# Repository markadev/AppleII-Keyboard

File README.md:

# Apple II Keyboard Adapter

This is a simple Arduino project to allow connecting a PS/2 keyboard to the
16 pin DIP keyboard connector on an Apple II. I've tested it on a
ReactiveMicro reproduction Apple II+ RFI logic board and it works great.

All keys are mapped to modern keyboard equivalents and the Apple can be
reset with the Ctrl-PrtScrn key combo.

I've built this project two different ways - the original prototype with a cheap Arduino Pro
Micro clone, and a newer version that consolidates all the wiring onto a small PCB with an
ATtiny24a microcontroller. This is very much a DIY project.

## ATtiny24a version

This version of the keyboard adapter is pretty simple and also includes a footprint for optional
ESD protection diodes to protect your Apple II from static discharges through the PS/2 interface.
It will require an ATtiny ISP (In-system Programmer) like the XGecu T48 or similar, or an Arduino
running the ArduinoISP sketch could also work.

It's composed of two parts: an adapter board with a microcontroller for performing the
translation logic and a connector board with the PS/2 keyboard connector that can be mounted
separately. If you want to use a different type of PS/2 connector then you are free to wire
up anything you need to the 8 pin header on the adapter board! For example, I can use an old
PC screw-mounted PS/2 connector.

### Building

This repo contains all the source files for building a Keyboard Adapter:
 * [KiCad project for the adapter board](./AppleII-Keyboard)
 * [KiCad project for a mountable PS/2 connector board](./AppleII-Keyboard-Connector)
 * [Source code for the microcontroller](./src/AppleII_PS2_Keyboard)

All the output files are also included so you don't need to install KiCad or the Arduino IDE if
you don't want to.
 * Schematics for the [adapter board](./AppleII-Keyboard/AppleII-Keyboard.pdf) and [connector board](./AppleII-Keyboard-Connector/AppleII-Keyboard-Connector.pdf)
 * Gerber files for the [adapter board](./AppleII-Keyboard/outputs/) and [connector board](./AppleII-Keyboard-Connector/outputs/)
 * [Pre-compiled ATtiny code](./src/AppleII_PS2_Keyboard/build/diy_attiny.avr.attiny24_diy/AppleII_PS2_Keyboard.ino.hex) to flash into the ATtiny

#### Parts List

Most of the parts are commodity and can be substituted for others, except for the ATtiny and the
ESD protection diodes. The ESD diodes are OPTIONAL so can be omitted if you can't find them or have
difficulty soldering the small surface-mount part.

You'll need one of each PCB; one PCB for the adapter that plugs into the keyboard connector on the
Apple II logic board and one PCB for the PS/2 mini-DIN connector board.

| Qty | Value                     | Mfr                 | MfrPartNo          | MouserPartNo         |
|-----|---------------------------|---------------------|--------------------|----------------------|
|  1  | 1x16 Machine Pin Header   | Samtec              | TS-116-T-A         | 200-TS116TA          |
|  1  | DIP-14 Socket             | TE Connectivity     | 1-2199298-3        | 571-1-2199298-3      |
|  1  | ATtiny24a                 | Microchip           | ATTINY24A-PU       | 556-ATTINY24A-PU     |
|  1  | 0.1uF                     | Vishay              | A104K15X7RF5TAA    | 594-A104K15X7RF5TAA  |
|  1  | Breakaway 2x8 pin headers | Amphenol            | 10129381-916001BLF | 649-1012938191601BLF |
|  1  | ESD Protection Diodes     | Diodes Incorporated | DT2042-04TS-7      | 621-DT2042-04TS-7    |
|  1  | Mini-DIN-6 connector      | Kycon               | KMDGX-6S-BS        | 806-KMDGX-6S-BS      |
|  2  | 2x4P IDC cable housing    | Amphenol            | 71600-008LF        | 649-71600-008LF      |

In addition to these components you will also need some 8 conductor 1.27mm pitch ribbon cable for
the cable between the adapter board and the connector board, as long as you need to reach wherever
you'll be mounting the PS/2 connector. This type of ribbon cable can be scavenged from common internal
cables that were used in old PCs.

#### Assembling

First, use a sharp thin knife on a solid surface (with protection) to split the 1x16 and 2x8 pin headers
in half so you end up with 2 1x8 machine pin headers and 2 2x4 square pin heders.

Then you can solder one of the 2x4 headers and the mini-DIN-6 connector to the connector board.

Soldering together the adapter board is a little more involved:
 1. If you have the ESD protection diode then carefully solder them on first. Pin 1 on the tiny package
    is marked with a dot that you may need a strong light and magnifying glass to see. This pin is marked
    on the PCB with a small triangle. After soldering on, check for shorts between any of the solder joints
    before continuing.
 2. The two 8-machine-pin headers should be installed next on the **underside** of the board as the
    silkscreen is facing you. The board's silkscreen has an IC outline that the two pin headers will be
    installed around. Since the headers are on the underside of the board you will be soldering on the top
    of the board around that IC outline.

    It helps to keep the pin headers straight if you insert them into a solderless breadboard or protoboard
    and then rest the PCB on top while soldering them in place.
 3. Install the DIP-14 IC socket on the top side of the board oriented so that pin 1 is pointed to by the
    triangle on the silkscreen. The IC sockets referenced in the part list will easily clear the solder
    joints of the pin headers from step 2 but if yours don't then you'll have to file a channel so they do.

    Half of the socket's pins will be between the two pin headers from step 2 so getting the soldering iron
    to them is a little tight.
 4. Install the decoupling capacitor on the top side of the board and solder in place.

To assemble the 8 pin ribbon cable just make sure that the same wire is entering the marked pin 1 position
on both connector housings. The ribbon cable can enter either side of the housing as long as that wire lines
up with the pin 1 position.

#### Flashing the ATtiny

These steps will vary depending on the programmer and software you use. I can confirm that the XGecu T48
programmer works but I am sure there are many others. An Arduino running the ArduinoISP sketch should also
work (though setting fuse values looks much more complicated).

1. Select the ATtiny24a device (DIP14 packaging if the different packages are listed) in your programming software.
2. Load [the .hex file](./src/AppleII_PS2_Keyboard/build/diy_attiny.avr.attiny24_diy/AppleII_PS2_Keyboard.ino.hex)
   into your programming software. Make sure to load it as a hex file and not as a binary file.
3. Find and open the tab or dialog box to set the ATtiny fuse values. In the Xgpro application these settings are
   on the "Config" tab.
   * clear CKDIV8=0  (to disable clock division by 8)
4. Program the ATtiny

## Arduino Pro Micro version

#### Parts list
 1. Arduino. I used a cheap Arduino Pro Micro clone from Amazon but
    you could probably adapt to use whatever you have on hand.
 2. Female PS/2 connector
 3. 2 8-pin male machine pin headers, or some other connector for the
    DIP-16 socket on the Apple II logic board.

#### Assembling

_Warning_: The DIP-16 connector on the logic board does have some pins with
higher voltages that will destroy your Arduino if you accidentally connect to
them, so take care.

The Arduino hole pattern is too wide for the DIP-16 socket so I used another
PCB to hold the machine pins and then jumpered the Arduino to the pins on top.
I also used a pin header to connect to a spare PS/2 connector from an old PC.

It's not so pretty, but it's compact and cost almost nothing.

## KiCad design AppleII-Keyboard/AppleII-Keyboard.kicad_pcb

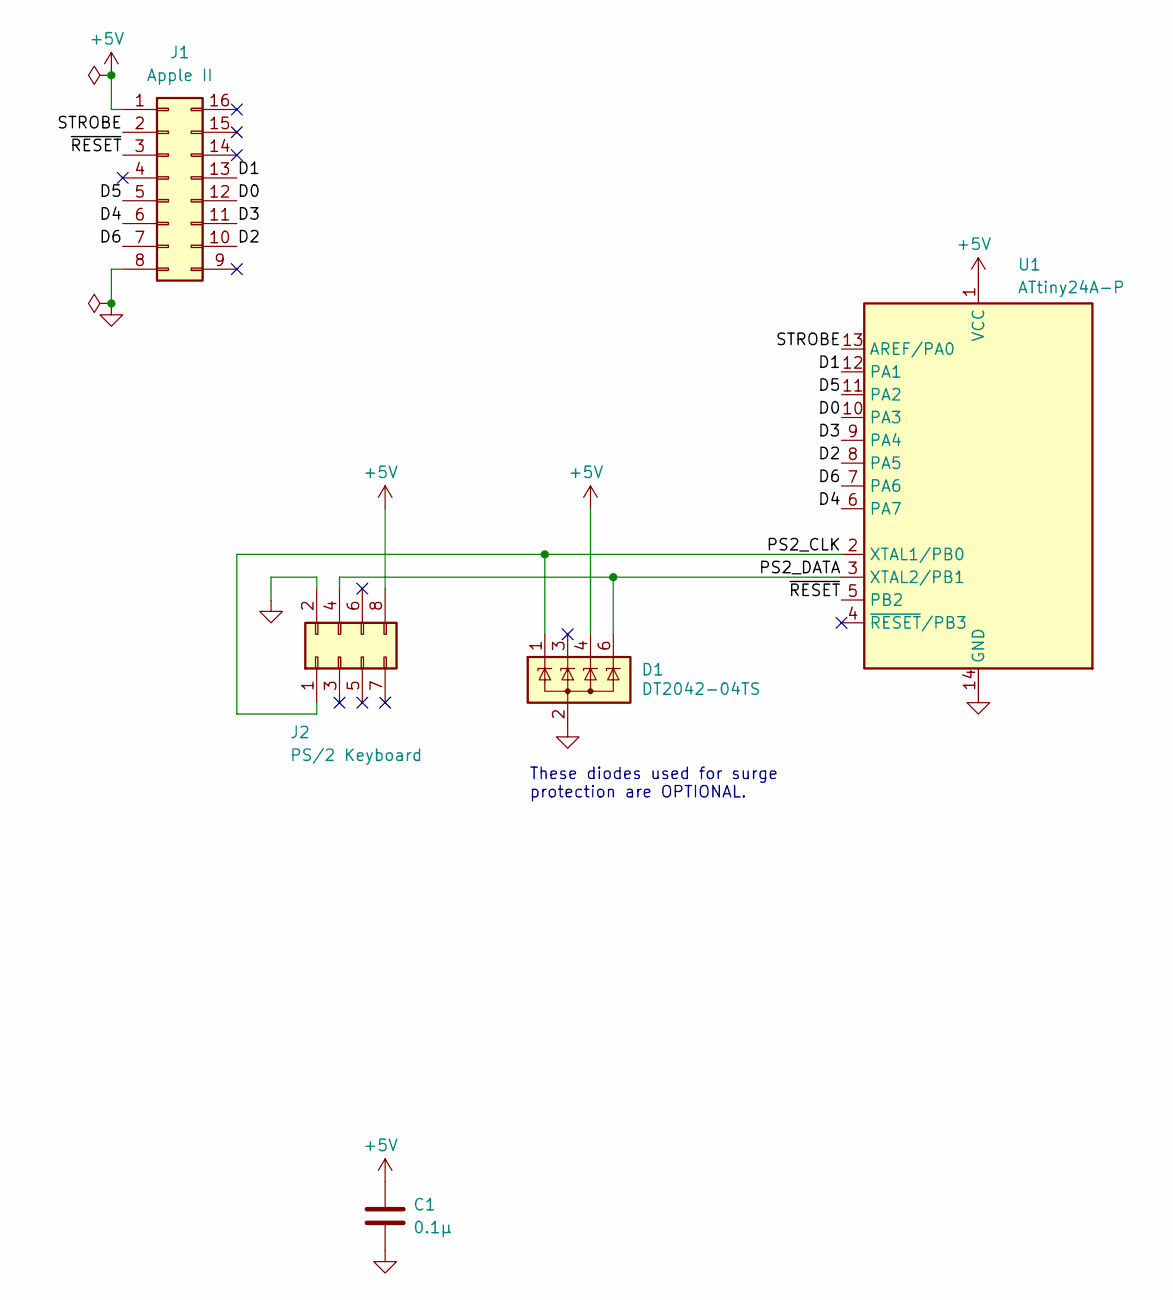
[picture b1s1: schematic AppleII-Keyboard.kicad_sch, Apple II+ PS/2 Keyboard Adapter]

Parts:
C1: 0.1µ; C_Axial_L3.8mm_D2.6mm_P7.50mm_Horizontal
D1: DT2042-04TS; TSOT-23-6_HandSoldering; MfrPartNo DT2042-04TS-7; MouserPartNo 621-DT2042-04TS-7
J1: Apple II; DIP-16_W7.62mm_UndersidePins
J2: PS/2 Keyboard; PinHeader_2x04_P2.54mm_Vertical
U1: ATtiny24A-P; DIP-14_W7.62mm_Socket; MfrPartNo ATTINY24A-PU; MouserPartNo 556-ATTINY24A-PU

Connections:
+5V: C1.1, D1.4 (K), J1.1, J2.8, U1.1 (VCC)
/D0: J1.12, U1.10 (PA3)
/D1: J1.13, U1.12 (PA1)
/D2: J1.10, U1.8 (PA5)
/D3: J1.11, U1.9 (PA4)
/D4: J1.6, U1.6 (PA7)
/D5: J1.5, U1.11 (PA2)
/D6: J1.7, U1.7 (PA6)
/PS2_CLK: D1.1 (K), J2.1, U1.2 (XTAL1/PB0)
/PS2_DATA: D1.6 (K), J2.4, U1.3 (XTAL2/PB1)
/STROBE: J1.2, U1.13 (AREF/PA0)
/~RESET: J1.3, U1.5 (PB2)
GND: C1.2, D1.2 (A), J1.8, J2.2, U1.14 (GND)

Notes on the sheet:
These diodes used for surge protection are OPTIONAL.

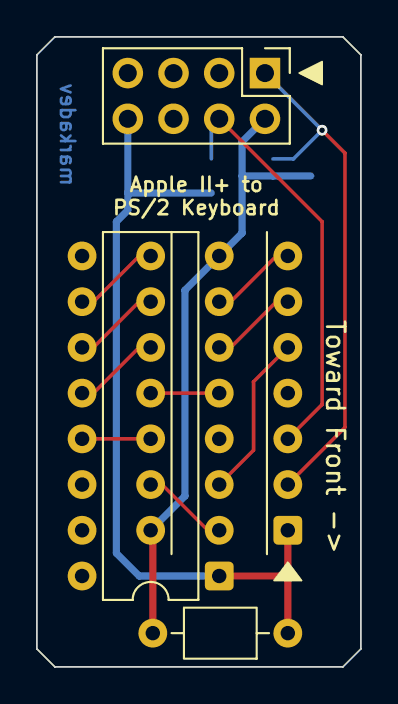
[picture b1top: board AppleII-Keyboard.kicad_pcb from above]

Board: 2 copper layers, 18.0 x 35.0 mm, 5 parts (1 on the bottom side), 13 nets.

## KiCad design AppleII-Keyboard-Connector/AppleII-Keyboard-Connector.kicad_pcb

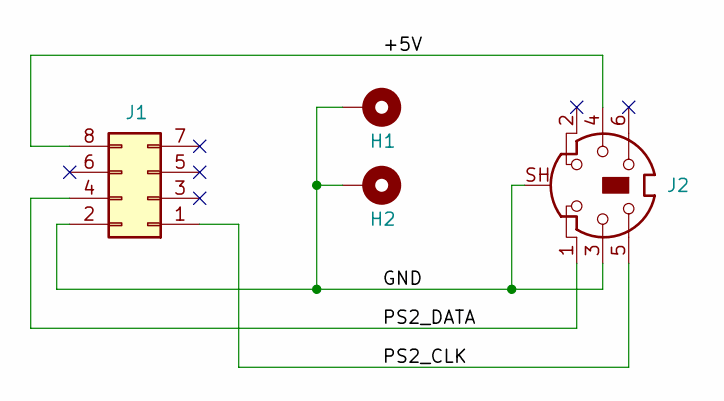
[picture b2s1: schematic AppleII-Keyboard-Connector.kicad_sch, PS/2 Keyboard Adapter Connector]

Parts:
H1, H2: MountingHole_Pad; MountingHole_3.2mm_M3_DIN965_Pad
J1: Conn_02x04_Odd_Even; PinHeader_2x04_P2.54mm_Vertical
J2: Shielded-Mini-DIN-6; Mini_DIN_round_6_canned

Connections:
/+5V: J1.8, J2.4
/GND: H1.1, H2.1, J1.2, J2.3, J2.SH
/PS2_CLK: J1.1, J2.5
/PS2_DATA: J1.4, J2.1

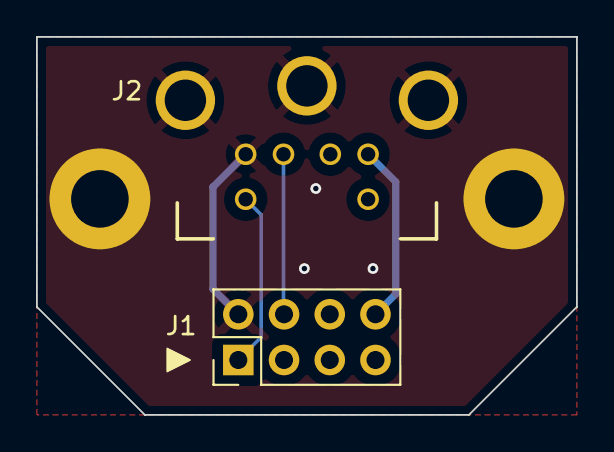
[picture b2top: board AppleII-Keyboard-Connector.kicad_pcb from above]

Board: 2 copper layers, 30.0 x 21.0 mm, 4 parts (0 on the bottom side), 4 nets.

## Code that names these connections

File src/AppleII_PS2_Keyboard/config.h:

#pragma once

#if defined(ARDUINO_ATTINY24_DIY)

// PS/2 interface configuration
#define PS2_CLOCK_PIN  10   /* PB0 */
#define PS2_DATA_PIN   9    /* PB1 */
#define PS2_RX_BUFFER_SIZE 16

// AppleII interface configuration
#define AII_RESET_PIN  8    /* PB2 */
#define AII_STROBE_PIN 0    /* PA0 */
#define AII_DATA_PIN_0 3    /* PA3 */
#define AII_DATA_PIN_1 1    /* PA1 */
#define AII_DATA_PIN_2 5    /* PA5 */
#define AII_DATA_PIN_3 4    /* PA4 */
#define AII_DATA_PIN_4 7    /* PA7 */
#define AII_DATA_PIN_5 2    /* PA2 */
#define AII_DATA_PIN_6 6    /* PA6 */

#else

// PS/2 interface configuration
#define PS2_CLOCK_PIN 7
#define PS2_DATA_PIN 8
#define PS2_RX_BUFFER_SIZE 16

// AppleII interface configuration
#define AII_RESET_PIN 0
#define AII_STROBE_PIN 1
#define AII_DATA_PIN_0 20
#define AII_DATA_PIN_1 21
#define AII_DATA_PIN_2 18
#define AII_DATA_PIN_3 19
#define AII_DATA_PIN_4 4
#define AII_DATA_PIN_5 3
#define AII_DATA_PIN_6 5

#endif

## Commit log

2021-12-29 Add a readme
2021-12-29 Update the readme
2021-12-29 Add some more to the readme
2025-10-03 Fix idle level of the /RESET line.
    The /RESET line driver should be open-collector so don't drive it high - leave it floating
    (as a pin input) and only drive it low when asserting the signal.
2025-10-14 Reduce code space use for ATtiny support
    Store the scancode translation table more efficiently so the entire sketch
    can fit into a 2KB ATtiny
2025-10-14 Commit custom PCB kicad projects
2025-10-14 Minor cleanup of the PS2 classes and added ATtiny24 support
2025-10-14 Update documentation with the new hardware information
2025-10-14 Fix whitespace in the Arduino code
2025-10-14 Commit the precompiled ATtiny program
2025-10-14 Clarify text in README
2025-10-14 fix formatting
2025-10-14 Update copyright date

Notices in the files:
AppleII-Keyboard-Connector/AppleII-Keyboard-Connector.kicad_pcb:
Licensed under CERN-OHL-P V2.0 (https://ohwr.org/cern_ohl_p_v2.txt)
Copyright (C) 2025 Mark Aikens
